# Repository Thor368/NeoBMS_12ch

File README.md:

# NeoBMS_12ch
Flexible NeoBMS slave board with 12 channels to connect to the battery.

## V1.0
- slave board with internal balancing switches
- 100mA per channel max
- 400mA per slave max
- expansion connector for temp/current measurment board

## V2.0
- slave board with external balancing switches
- 100mA per channel max
- should improve measurement accuracy (no heat in chip)

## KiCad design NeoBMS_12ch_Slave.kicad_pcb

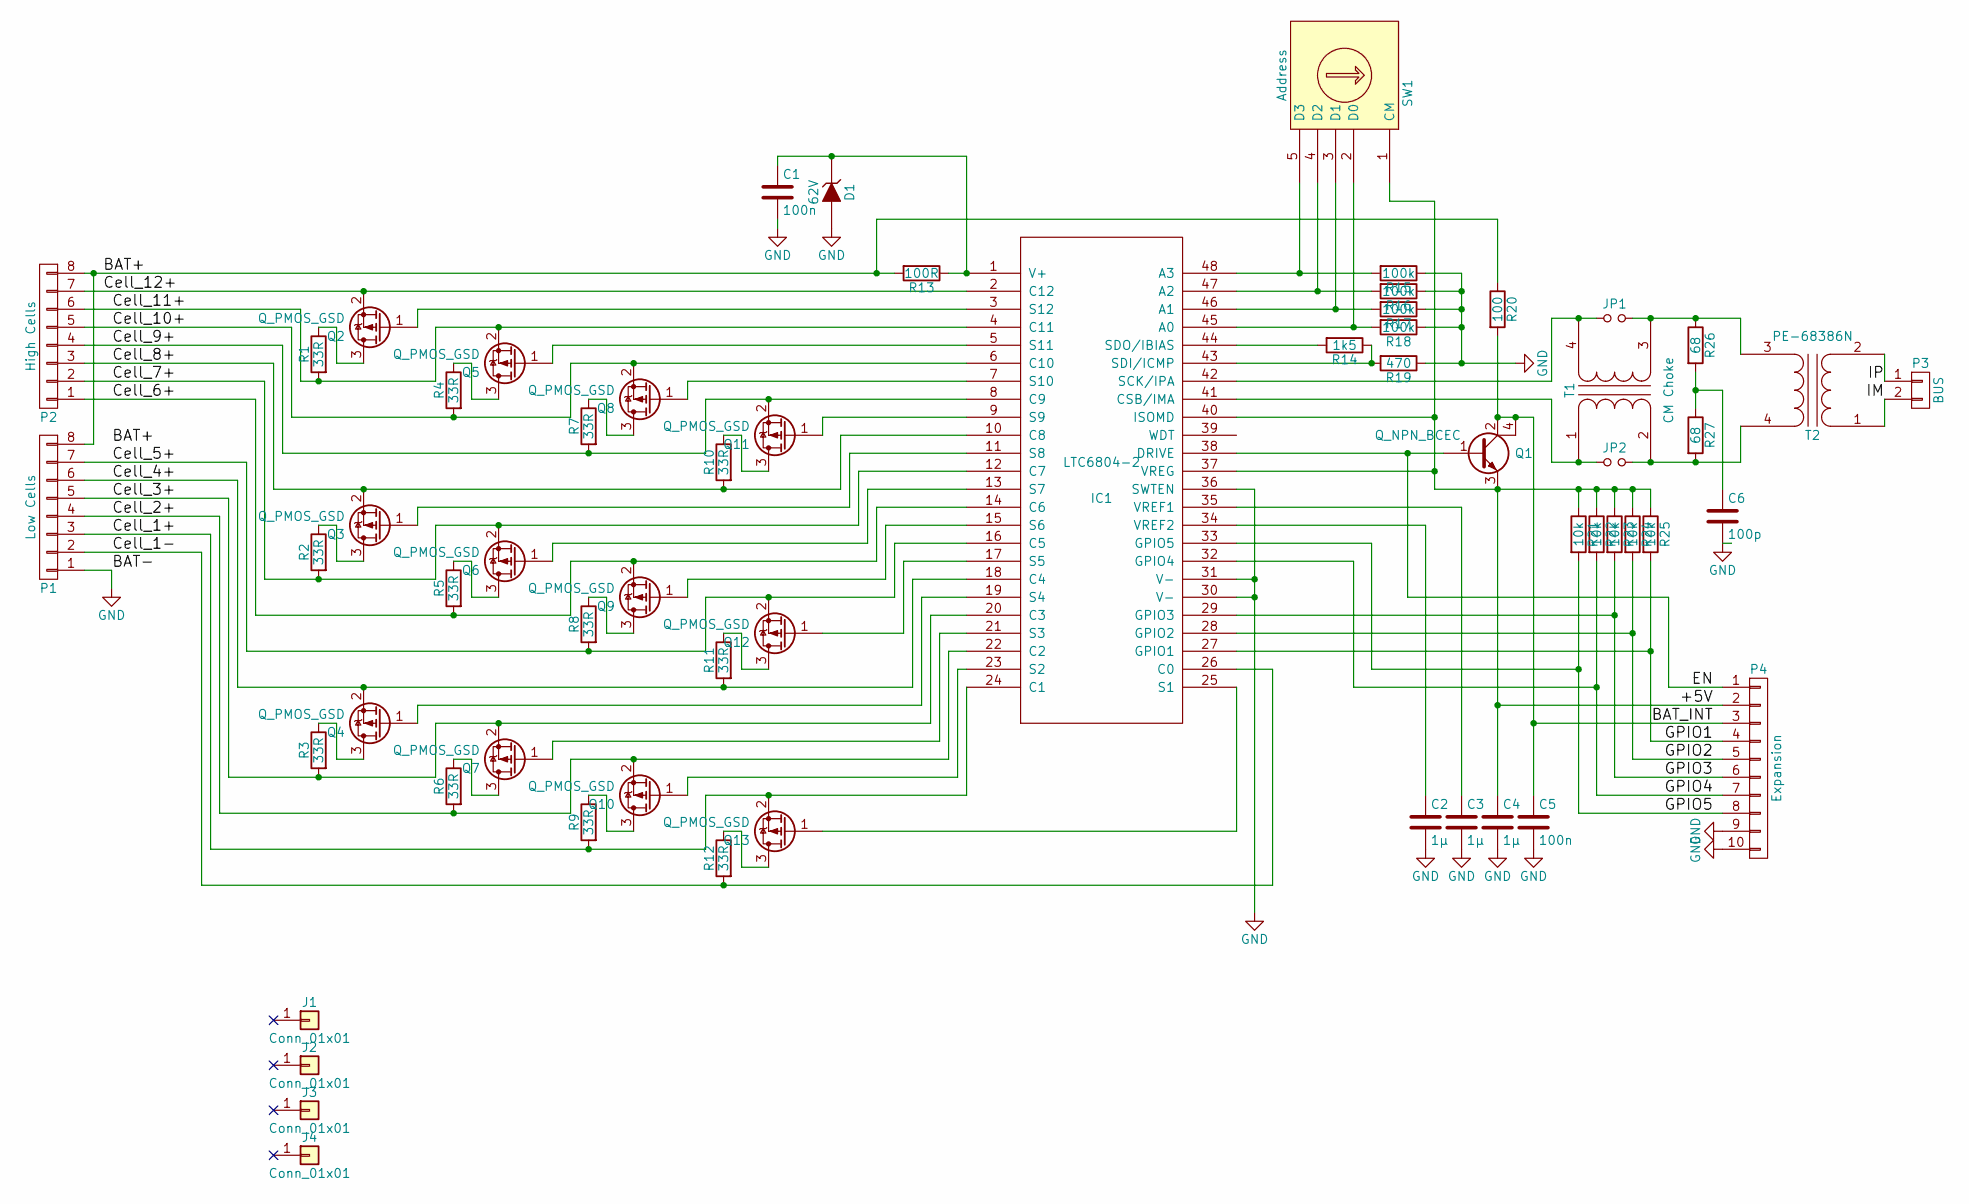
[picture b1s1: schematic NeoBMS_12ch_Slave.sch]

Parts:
C1, C5: 100n; C_0805
C2, C3, C4: 1µ; C_0805
C6: 100p; C_0805
D1: 62V; MiniMELF_Standard
IC1: LTC6804-2; TSSOP-48_6.1x12.5mm_Pitch0.5mm
J1, J2, J3, J4: Conn_01x01; MountingHole_3.5mm
JP1, JP2: Jumper_NO_Small; Jumper_2
P1: Low Cells; WAGO_micro_8
P2: High Cells; WAGO_micro_8
P3: BUS; WAGO_micro_2
P4: Expansion; pin_array_2x5_lock
Q1: Q_NPN_BCEC; SOT-223
Q2, Q3, Q4, Q5, Q6, Q7, Q8, Q9, Q10, Q11, Q12, Q13: Q_PMOS_GSD; SOT-23
R1, R2, R3, R4, R5, R6, R7, R8, R9, R10, R11, R12: 33R; R_1210
R13: 100R; R_0805
R14: 1k5; R_0805
R15, R16, R17, R18: 100k; R_0805
R19: 470; R_0805
R20: 100; R_0805
R21, R22, R23, R24, R25: 10k; R_0805
R26, R27: 68; R_0805
SW1: Address; Codingswitch
T1: CM Choke; DLW43S
T2: PE-68386N; PE-68386NL

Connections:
/+5V: C4.1, IC1.37 (VREG), IC1.40 (ISOMD), P4.2, Q1.3 (E), R21.1, R22.1, R23.1, R24.1, R25.1, SW1.1 (CM)
/BAT+: P1.8, P2.8, R13.2, R20.1
/BAT_INT: C5.1, P4.3, Q1.2 (C), Q1.4 (C), R20.2
/Cell_1+: IC1.24 (C1), P1.3, Q13.2 (S), R9.2
/Cell_1-: IC1.26 (C0), P1.2, R12.2
/Cell_2+: IC1.22 (C2), P1.4, Q10.2 (S), R6.2
/Cell_3+: IC1.20 (C3), P1.5, Q7.2 (S), R3.2
/Cell_4+: IC1.18 (C4), P1.6, Q4.2 (S), R11.2
/Cell_5+: IC1.16 (C5), P1.7, Q12.2 (S), R8.2
/Cell_6+: IC1.14 (C6), P2.1, Q9.2 (S), R5.2
/Cell_7+: IC1.12 (C7), P2.2, Q6.2 (S), R2.2
/Cell_8+: IC1.10 (C8), P2.3, Q3.2 (S), R10.2
/Cell_9+: IC1.8 (C9), P2.4, Q11.2 (S), R7.2
/Cell_10+: IC1.6 (C10), P2.5, Q8.2 (S), R4.2
/Cell_11+: IC1.4 (C11), P2.6, Q5.2 (S), R1.2
/Cell_12+: IC1.2 (C12), P2.7, Q2.2 (S)
/EN: IC1.38 (DRIVE), P4.1, Q1.1 (B)
/GPIO1: IC1.27 (GPIO1), P4.4, R25.2
/GPIO2: IC1.28 (GPIO2), P4.5, R24.2
/GPIO3: IC1.29 (GPIO3), P4.6, R23.2
/GPIO4: IC1.32 (GPIO4), P4.7, R22.2
/GPIO5: IC1.33 (GPIO5), P4.8, R21.2
/IM: P3.2, T2.1 (AA)
/IP: P3.1, T2.2 (AB)
GND: C1.2, C2.2, C3.2, C4.2, C5.2, C6.2, D1.2 (A), IC1.30 (V-), IC1.31 (V-), IC1.36 (SWTEN), P1.1, P4.9, P4.10, R15.1, R16.1, R17.1, R18.1, R19.1
unnamed: C1.1, D1.1 (K), IC1.1 (V+), R13.1
unnamed: C2.1, IC1.34 (VREF2)
unnamed: C3.1, IC1.35 (VREF1)
unnamed: C6.1, R26.2, R27.1
unnamed: IC1.3 (S12), Q2.1 (G)
unnamed: IC1.5 (S11), Q5.1 (G)
unnamed: IC1.7 (S10), Q8.1 (G)
unnamed: IC1.9 (S9), Q11.1 (G)
unnamed: IC1.11 (S8), Q3.1 (G)
unnamed: IC1.13 (S7), Q6.1 (G)
unnamed: IC1.15 (S6), Q9.1 (G)
unnamed: IC1.17 (S5), Q12.1 (G)
unnamed: IC1.19 (S4), Q4.1 (G)
unnamed: IC1.21 (S3), Q7.1 (G)
unnamed: IC1.23 (S2), Q10.1 (G)
unnamed: IC1.25 (S1), Q13.1 (G)
unnamed: IC1.41 (CSB/IMA), JP2.1, T1.1 (AA)
unnamed: IC1.42 (SCK/IPA), JP1.1, T1.4 (SB)
unnamed: IC1.43 (SDI/ICMP), R14.1, R19.2
unnamed: IC1.44 (SDO/IBIAS), R14.2
unnamed: IC1.45 (A0), R18.2, SW1.2 (D0)
unnamed: IC1.46 (A1), R17.2, SW1.3 (D1)
unnamed: IC1.47 (A2), R16.2, SW1.4 (D2)
unnamed: IC1.48 (A3), R15.2, SW1.5 (D3)
unnamed: JP1.2, R26.1, T1.3 (SA), T2.3 (SA)
unnamed: JP2.2, R27.2, T1.2 (AB), T2.4 (SB)
unnamed: Q2.3 (D), R1.1
unnamed: Q3.3 (D), R2.1
unnamed: Q4.3 (D), R3.1
unnamed: Q5.3 (D), R4.1
unnamed: Q6.3 (D), R5.1
unnamed: Q7.3 (D), R6.1
unnamed: Q8.3 (D), R7.1
unnamed: Q9.3 (D), R8.1
unnamed: Q10.3 (D), R9.1
unnamed: Q11.3 (D), R10.1
unnamed: Q12.3 (D), R11.1
unnamed: Q13.3 (D), R12.1

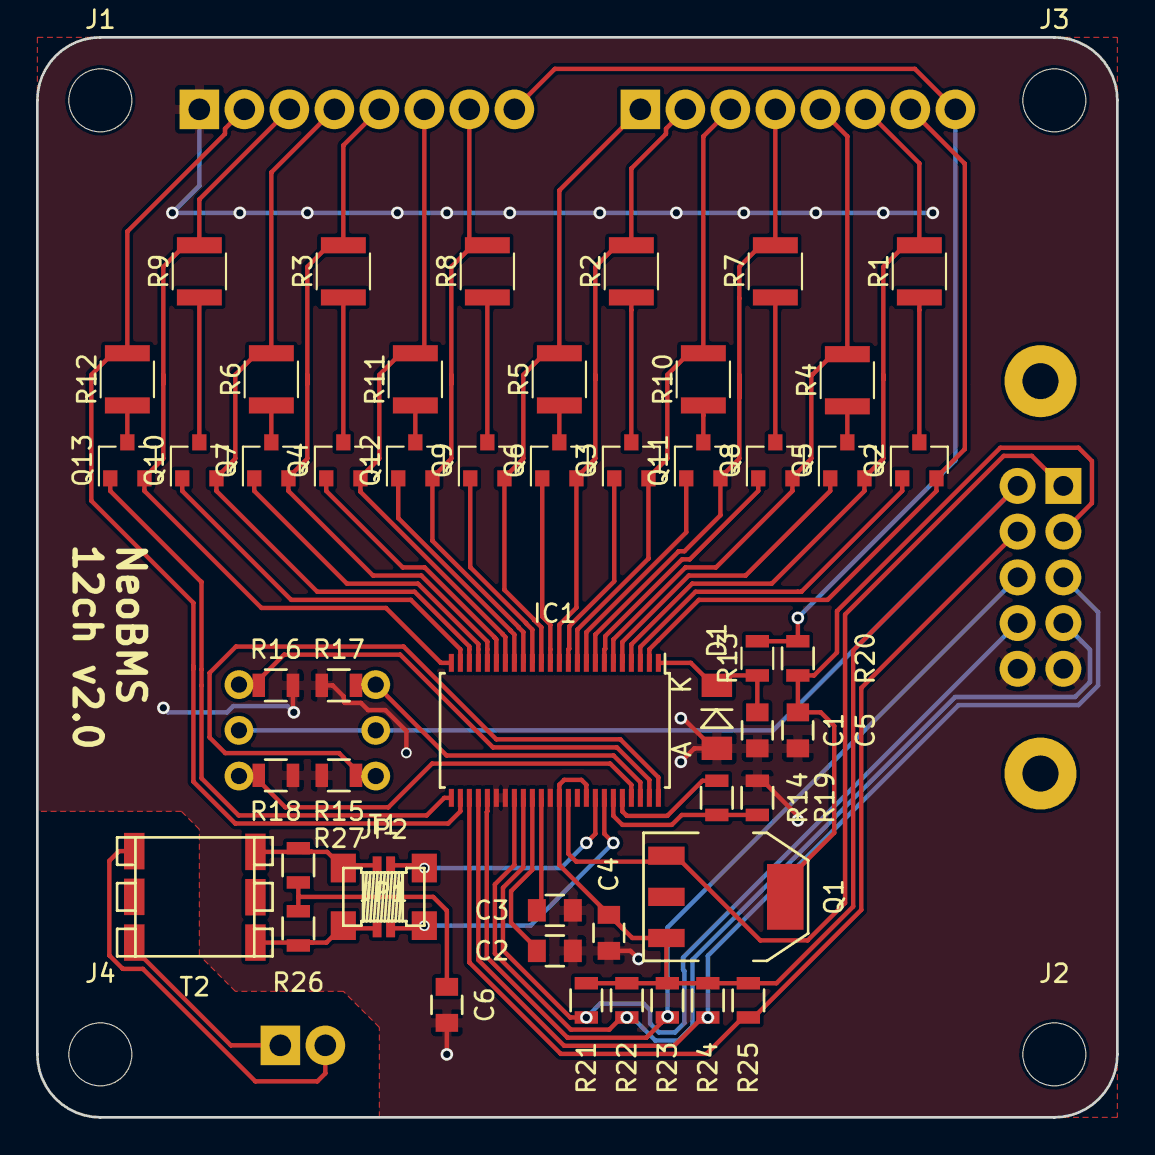
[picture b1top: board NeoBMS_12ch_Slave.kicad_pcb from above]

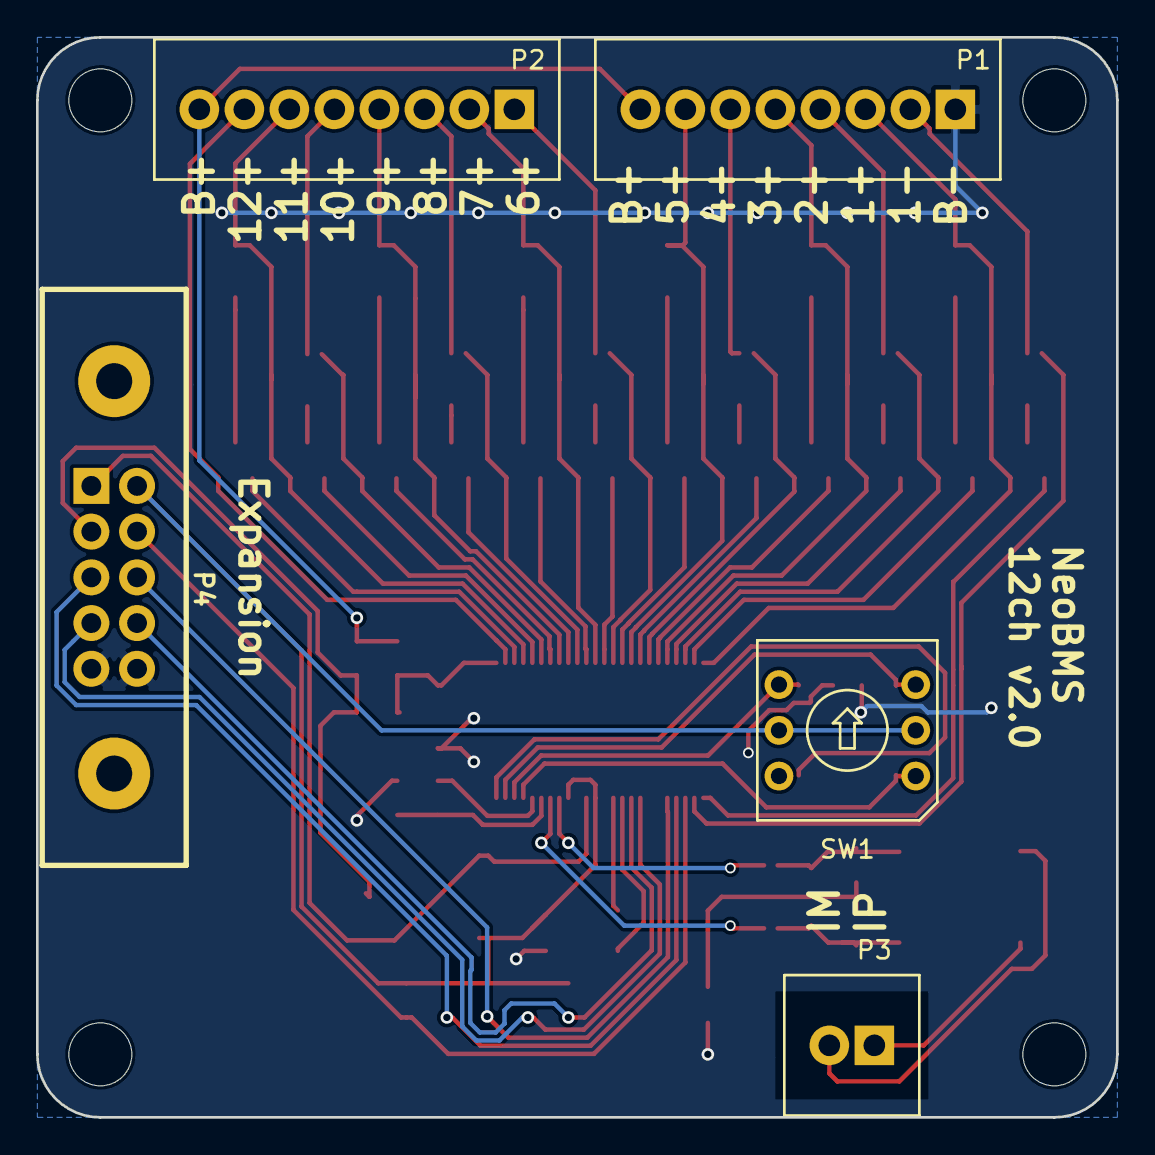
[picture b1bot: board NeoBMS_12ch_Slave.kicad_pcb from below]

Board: 2 copper layers, 60.0 x 60.0 mm, 61 parts (5 on the bottom side), 63 nets.

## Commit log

2018-03-08 - final version of the internal switched balancing circuit
2018-03-08 - integrated balancer and filter resistors into one - changed filter/balancer resistors to 1206 - changed BIAS network to 1k5 + 470R - relocated BIAS network
2018-03-10 - jump to version 2.0 - external balancing switches
2019-06-05 fixed typo
